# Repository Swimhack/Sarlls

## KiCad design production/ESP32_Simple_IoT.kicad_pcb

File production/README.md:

# ESP32 Simple IoT Switch - Rev 2 Controller Prototype

This directory contains the active SafeSwitch controller-board manufacturing
candidate. It is a USB-C-powered ESP32 relay controller used to validate the
control path before developing the complete automotive battery-disconnect
system.

## Board

| Parameter | Value |
|---|---|
| Size | 80 mm x 60 mm |
| Layers | 2 |
| Thickness | 1.6 mm FR-4 |
| Copper | 1 oz |
| Input | USB-C 5V |
| Logic | ESP32-WROOM-32, CP2102N USB-UART |
| Output | 5V relay dry contacts on J2 |

## Manufacturing Files

- `ESP32_Simple_IoT.kicad_pcb`: active generated PCB
- `ESP32_Simple_IoT_BOM.csv`: JLCPCB BOM, 20 line items
- `ESP32_Simple_IoT_CPL.csv`: placement list, 28 placements
- `ESP32_Simple_IoT_Gerbers.zip`: clean fabrication ZIP
- `Sarlls_IoT_Switch_Rev2_JLCPCB.zip`: identical Rev 2 fabrication ZIP
- `drc_report.json`: production DRC report

The fabrication ZIP contains only copper, mask, top paste, silkscreen, edge,
job, PTH drill, and NPTH drill files.

## DRC Status

Run `scripts/validate_drc.py` after every DRC export. Current expected result:

```text
DRC gate: 0 blocking, 26 approved J1 edge errors, 11 warnings
```

The 26 approved errors are limited to the intentional edge-mounted USB-C
contact row. Shorts, crossings, unconnected items, ordinary clearances, and
hole-clearance errors block release.

## Before Ordering

1. Confirm the assembler accepts the two small J1 VBUS via-in-pad escapes.
2. Confirm SW1, SW2, and J2 selected parts match their footprints.
3. Review the assembler DFM report and placement preview.
4. Confirm all BOM parts are available.

## Firmware

- `firmware/wifi_switch.ino`: local WiFi web/API controller; default ESP32
  partition.
- `firmware/test_firmware.ino`: hardware test image; requires the `huge_app`
  partition.

Rev 1 physical boards have not yet completed USB enumeration, flashing, and
relay bring-up. Rev 2 is therefore a pre-fabrication candidate, not a validated
production board.

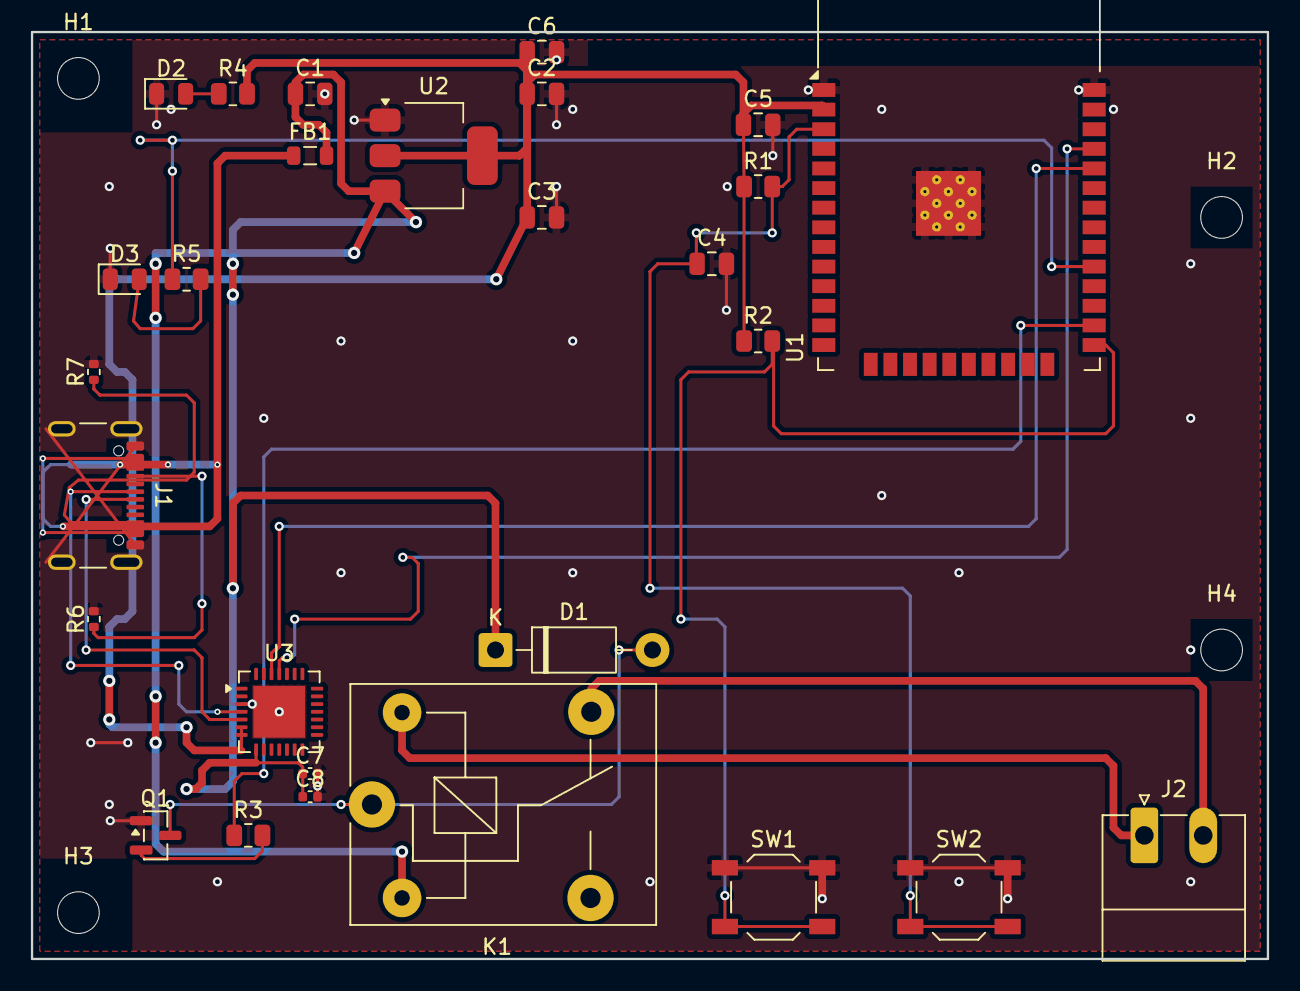
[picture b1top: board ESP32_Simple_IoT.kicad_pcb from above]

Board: 2 copper layers, 80.0 x 60.0 mm, 32 parts (0 on the bottom side), 20 nets.

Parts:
C1, C2, C3, C4, C5, C6: C_0805_2012Metric
C7, C8: C_0402_1005Metric
D1: D_DO-41_SOD81_P10.16mm_Horizontal
D2, D3: LED_0805_2012Metric
FB1: L_0805_2012Metric
H1, H2, H3, H4: MountingHole_2.7mm_M2.5
J1: USB_C_Receptacle_GCT_USB4105-xx-A_16P_TopMnt_Hori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; USB_C_Receptacle_GCT_USB4105-xx-A_16P_TopMnt_Horizontal
J2: PhoenixContact_MC_1,5_2-G-3.81_1x02_P3.81mm_Horiz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; PhoenixContact_MC_1,5_2-G-3.81_1x02_P3.81mm_Horizontal
K1: Relay_SPDT_SANYOU_SRD_Series_Form_C
Q1: SOT-23
R1, R2, R3, R4, R5: R_0805_2012Metric
R6, R7: R_0402_1005Metric
SW1, SW2: SW_SPST_TL3342
U1: ESP32-WROOM-32
U2: SOT-223-3_TabPin2
U3: QFN-28-1EP_5x5mm_P0.5mm_EP3.35x3.35mm

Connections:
+3V3: C2.1, C3.1, C5.1, C6.1, R1.1, R2.1, R4.2, U1.2, U2.2, U3.6, U3.7
+5V: C1.1, C7.1, C8.1, D1.1, FB1.2, K1.2, U2.3, U3.8
CC1: J1.A5, R6.1
CC2: J1.B5, R7.1
ESP_EN: C4.1, R1.2, SW2.2, U1.3
ESP_IO0: R2.2, SW1.2, U1.25
ESP_IO4: R3.1, U1.26
ESP_IO5: R5.1, U1.29
ESP_RX: U1.34, U3.26
ESP_TX: U1.35, U3.25
GND: C1.2, C2.2, C3.2, C4.2, C5.2, C6.2, C7.2, C8.2, D2.1, D3.1, J1.A1, J1.A12, J1.B1, J1.B12, J1.S1, Q1.1, R6.2, R7.2, SW1.1, SW2.1, U1.1, U1.38, U1.39, U2.1, U3.3, U3.29
LED_PWR: D2.2, R4.1
LED_RELAY: D3.2, R5.2
RELAY_BASE: Q1.2, R3.2
RELAY_COIL: D1.2, K1.1, Q1.3
RELAY_COM: J2.1, K1.5
RELAY_NO: J2.2, K1.4
USB_D+: J1.A6, U3.4
USB_D-: J1.A7, U3.5
VBUS: FB1.1, J1.A4, J1.A9, J1.B4, J1.B9

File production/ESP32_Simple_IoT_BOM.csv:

Comment,Designator,Footprint,LCSC Part Number
ESP32-WROOM-32,U1,RF_Module:ESP32-WROOM-32,C82899
AMS1117-3.3,U2,Package_TO_SOT_SMD:SOT-223-3_TabPin2,C6186
CP2102N-A02-GQFN28,U3,Package_DFN_QFN:QFN-28-1EP_5x5mm_P0.5mm_EP3.35x3.35mm,C6568
BC817,Q1,Package_TO_SOT_SMD:SOT-23,C2137
SRD-05VDC-SL-C,K1,Relay_THT:Relay_SPDT_SANYOU_SRD_Series_Form_C,C35449
1N4007,D1,Diode_THT:D_DO-41_SOD81_P10.16mm_Horizontal,C106903
LED Green,D2,LED_SMD:LED_0805_2012Metric,C375456
LED Red,D3,LED_SMD:LED_0805_2012Metric,C84256
10uF,"C1,C2",Capacitor_SMD:C_0805_2012Metric,C15850
100nF,"C3,C4,C5",Capacitor_SMD:C_0805_2012Metric,C49678
10K,"R1,R2",Resistor_SMD:R_0805_2012Metric,C17414
1K,"R3,R4,R5",Resistor_SMD:R_0805_2012Metric,C17513
Ferrite Bead,FB1,Inductor_SMD:L_0805_2012Metric,C127284
Tactile Switch,"SW1,SW2",Button_Switch_SMD:SW_SPST_TL3342,C127509
USB_C_Receptacle,J1,Connector_USB:USB_C_Receptacle_GCT_USB4105-xx-A_16P_TopMnt_Horizontal,C165948
Terminal Block 2-pos,J2,Connector_Phoenix_MC:PhoenixContact_MC_1.5_2-G-3.81_1x02_P3.81mm_Horizontal,C8269

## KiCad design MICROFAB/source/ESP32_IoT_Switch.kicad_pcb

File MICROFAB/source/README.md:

# ESP32 IoT Switch — Source Design Files

Original KiCad PCB and Flux.ai exports. Edit these to modify the design.

## Files
- ESP32_IoT_Switch.kicad_pcb: KiCad 6 PCB layout (open with KiCad)
- flux_export_gerbers/: Gerbers from Flux.ai (INCOMPLETE — back copper and drill empty)
- IOT_SWITCH.zip / IOT_SWITCH2.zip: Original Flux.ai project exports
- options.csv: Component options/alternatives
- overview.md.txt: Project description

## Project
IoT switch to connect/disconnect a 12V car battery using an ESP32 + relay via WiFi.
Design uses discrete PFET approach.
Flux.ai project: https://www.flux.ai/swimhack/opposite-black-robot-vacuum

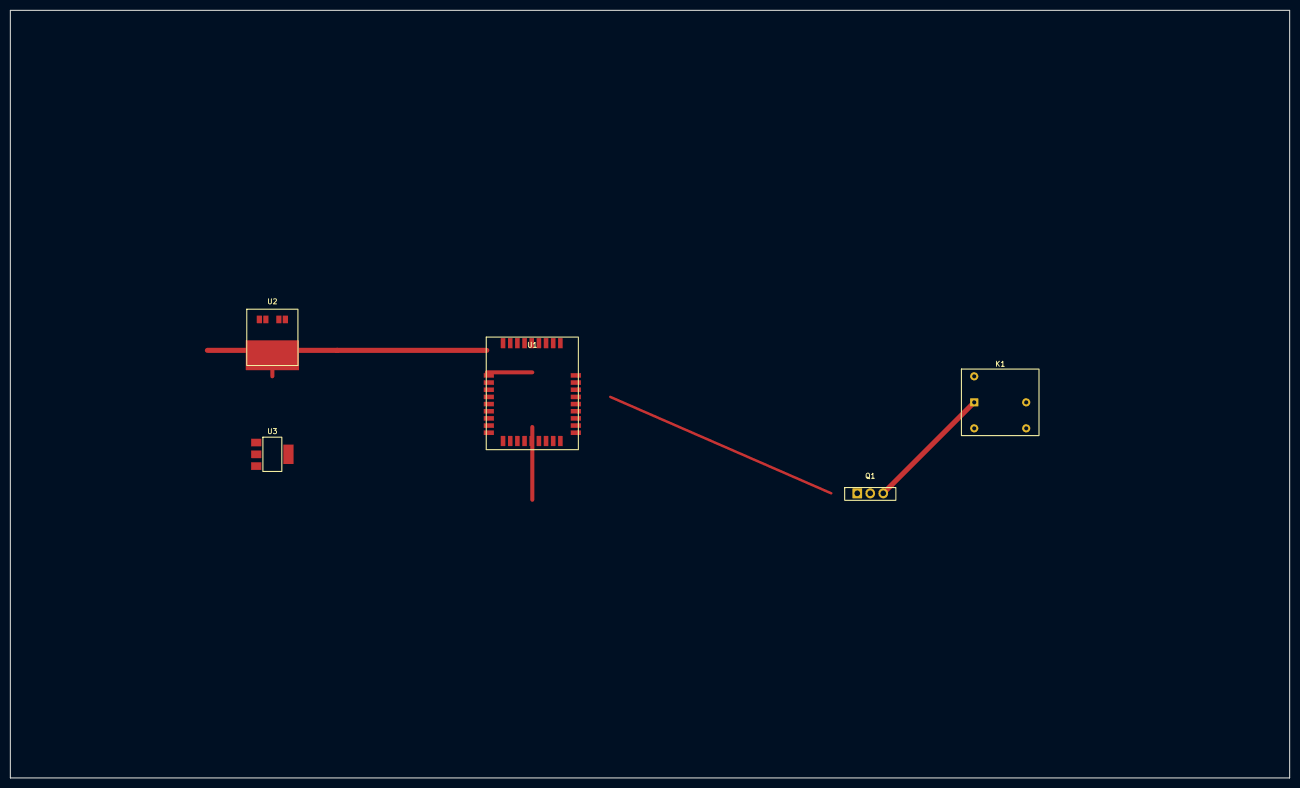
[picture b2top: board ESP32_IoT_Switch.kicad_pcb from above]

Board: 2 copper layers, 250.0 x 150.0 mm, 5 parts (0 on the bottom side), 7 nets.

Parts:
K1: G5LE-1; Relay_SPDT_Omron_G5LE-1
Q1: IRLZ44N; TO-220-3_Vertical
U1: ESP32-WROOM-32
U2: LM2596S-3.3; TO-263-5_TabPin3
U3: AMS1117-5.0; SOT-223-3_TabPin2

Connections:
+3V3: U1.2 (VDD), U2.2 (OUT), U3.3 (VI)
+5V: K1.2, U3.2 (VO)
+12V: U2.1 (VIN), U2.5 (~ON/OFF)
GND: K1.5, Q1.2 (S), U1.1 (GND), U1.15 (GND), U2.3 (GND), U3.1 (ADJ/GND)
unnamed: K1.1, Q1.3 (D)
unnamed: Q1.1 (G), U1.29 (IO5)
VCC: U1.3 (EN), U1.33 (RXD0), U1.34 (TXD0)

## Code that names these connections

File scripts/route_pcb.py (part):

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    add_via(board, net('+5V'), via_5v_u3_end[0], via_5v_u3_end[1], VIA_PWR_SIZE, VIA_PWR_DRILL)
    # F.Cu: (10,49) -> (11,49) -> (11,47.3) -> (14.5,47.3) at PWR_W
    # Then (14.5,47.3) -> U3:8 at SIG_W (narrower to clear U3:9 at x=15)
    # y=47.3 adds clearance from U3 bottom pads, stays clear of ESP_IO4 at y=48
    route_polyline(board, net('+5V'), F_Cu, PWR_W, [
        via_5v_u3_end,              # (10, 49)
        (11, 49),                   # Right to x=11
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    p_tx_esp = p('U1', '35')  # Right side of ESP32
    p_tx_u3 = p('U3', '25')   # Left side of U3

    # ESP_TX: stub -> via at (67, pin_y) -> down to y=34 -> left to x=24 -> via -> stub to U3
    via_tx_r = (67, p_tx_esp[1])
    add_track(board, net('ESP_TX'), F_Cu, SIG_W, p_tx_esp[0], p_tx_esp[1], via_tx_r[0], via_tx_r[1])
    add_via(board, net('ESP_TX'), via_tx_r[0], via_tx_r[1])
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        (16.5, 40.5), (p_tx_u3[0], 40.5), (p_tx_u3[0], p_tx_u3[1]),
    ])

    # ESP_RX: stub -> via at (65, pin_y) -> down to y=32 -> left to x=18 -> via -> stub to U3
    p_rx_esp = p('U1', '34')
    p_rx_u3 = p('U3', '26')
    via_rx_r = (65, p_rx_esp[1])
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    ])

    # ==========================================================
    # ESP_IO4 via B.Cu CHANNEL y=27
    # ==========================================================
    p_io4 = p('U1', '26')
    p_r3_1 = p('R3', '1')
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    ])

    # ==========================================================
    # ESP_IO5 via B.Cu CHANNEL y=6
    # ==========================================================
    p_io5 = p('U1', '29')
    p_r5_1 = p('R5', '1')
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        (43, 13), (43, p_c4_1[1]), p_c4_1,  # Down to C4:1 (43.05, 15)
    ])

    # ESP_EN: R1:2 -> U1:3 via x=49 corridor (avoiding ESP32 side pins)
    p_en = p('U1', '3')
    route_polyline(board, net('ESP_EN'), F_Cu, SIG_W, [
        p_r1_2,
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    # RELAY_COIL: D1:2 (anode) -> K1:1 via B.Cu bridge
    # D1:2 at (40.16,34), K1:1 at (22,50)
    # Both Q1:3 and D1:2 now meet at via (20, 50) for a strong joint
    # Via at y=38 to avoid ESP_TX B.Cu corridor at y=34
    p_d1_2 = p('D1', '2')
    route_manhattan(board, net('RELAY_COIL'), F_Cu, SIG_W, p_d1_2, (38, p_d1_2[1]), horiz_first=True)
    add_track(board, net('RELAY_COIL'), F_Cu, SIG_W, 38, p_d1_2[1], 38, 38)
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
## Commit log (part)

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2025-09-23 Initial commit from Specify template
2026-05-03 Fix duplicate include(':app') in settings.gradle.kts
2026-05-08 Daily order status update - 2026-05-08
    https://claude.ai/code/session_01U6yguS7baJEYNggUeRsDeD
2026-05-16 Daily order status update - 2026-05-16
2026-05-22 Daily order status update - 2026-05-22
    https://claude.ai/code/session_019r3tC1qqr2BCCJXo3rtssf
2026-05-24 Daily order status update - 2026-05-24
2026-05-27 Daily order status update - 2026-05-27
2026-05-28 Daily order status update - 2026-05-28
    https://claude.ai/code/session_01DTrkkFa5zWLoDzCyMMzbJC
2026-05-29 Daily order status update - 2026-05-29
    https://claude.ai/code/session_01Hf62nER5L6AKt14p1SVE7m
2026-05-30 Daily order status update - 2026-05-30
    https://claude.ai/code/session_011fs9fb4s9PijPbCiXGRP65
2026-05-31 Daily order status update - 2026-05-31
    https://claude.ai/code/session_013BASVTyHNosPHnqa4Uec1K
2026-06-01 Daily order status update - 2026-06-01
    https://claude.ai/code/session_01AqSQVcDaBj1aj3FJJK3D9x
2026-06-02 Daily order status update - 2026-06-02
    https://claude.ai/code/session_011U6SGD5v8EZ6BUGoWDGRfF
2026-06-03 Daily order status update - 2026-06-03
    https://claude.ai/code/session_01Xti3AkZH7frBXirByRzRoC
2026-06-04 Daily order status update - 2026-06-04
    https://claude.ai/code/session_011pFuVq5LWotPBjijX8DXey
2026-06-05 Daily order status update - 2026-06-05
    https://claude.ai/code/session_01VGRjsisZaFvaDe9MBmhxeP
2026-06-06 Daily order status update - 2026-06-06
    https://claude.ai/code/session_01SjEYTJ6s9gnxbphFHrWRY3
2026-06-07 Daily order status update - 2026-06-07
    https://claude.ai/code/session_01UDQJsrdQ9fH4NHhZbVQMPd
2026-06-07 feat: add SafeSwitch control room
2026-06-08 Daily order status update - 2026-06-08
    https://claude.ai/code/session_017wGQ2mB175MS9jWTaTuWcx
2026-06-09 Daily order status update - 2026-06-09
    https://claude.ai/code/session_01RZt6AopsTBXJzyL5vcESwj
2026-06-10 Daily order status update - 2026-06-10
    https://claude.ai/code/session_013KSy9XL1ZAVLYBcme6ADm7
2026-06-11 Daily order status update - 2026-06-11
2026-06-12 Daily order status update - 2026-06-12
    https://claude.ai/code/session_01RTh2i6RAzJKDAg4cH7rPp4
2026-06-13 Daily order status update - 2026-06-13
2026-06-14 Daily order status update - 2026-06-14
    https://claude.ai/code/session_013TwRxFEiDUF7rmHJA9wc7W
2026-06-15 Daily order status update - 2026-06-15
2026-06-16 Daily order status update - 2026-06-16
    https://claude.ai/code/session_01GriosYdF89Km396BXM8Dkg
2026-06-17 Daily order status update - 2026-06-17
2026-06-19 Daily order status update - 2026-06-19
2026-06-20 Daily order status update - 2026-06-20
2026-06-21 Daily order status update - 2026-06-21
2026-06-22 Daily order status update - 2026-06-22
2026-06-23 Daily order status update - 2026-06-23
2026-06-26 Daily order status update - 2026-06-26
2026-06-27 Daily order status update - 2026-06-27
2026-06-28 Daily order status update - 2026-06-28
2026-06-29 Daily order status update - 2026-06-29
